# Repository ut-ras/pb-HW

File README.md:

# pb-HW
Hardware for PacBot 2018

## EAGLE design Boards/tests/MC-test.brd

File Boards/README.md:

### Boards:

PCBs used (or designed for) [PacBot](https://harvardrobotics.com/pacbots/).

Tests:

- MC-test
    + A feature filled breakout board for the DRV8871 (doesn't work).
    + 

- MC-test-simple
    + Simplified barebones breakout board for the DRV8871, does work.

Robot:

- S0: Stage 0 PCB
    + Has shiny (16 APA102s), 2 voltage regulators (TPS76801QD), 2 ADCs (ADS1000), battery leads, an enable jumper, and passthrough pins for I2C, 5V, battery power, and SPI (CLK/MOSI).

- S0R: Stage 0 PCB, reduced
    + Same as above minus one voltage regulator and the enable jumper.
    + This board was tested; it likely has some cap ESR issues.

- S1: Stage 1 PCB
    + 4 Motor Drivers (DRV8871s), IMU (MPU-6050), Pololu Encoder module passthrough, and two I2C bus passthrough.
    + Janky but functional.
    + 

- Stage2_V2
    + 4 Distance Sensors + EN pin (VL6180Xs), an RPi Zero W, and 4 Motor PWM output pairs, 4 Quadrature Encoder inputs, 2 I2C Bus inputs, 1 SPI input (CLK/MOSI), 1 MPU interrupt pin, and assorted power connectors.
    + Not finished or routed, but a valiant effort regardless.

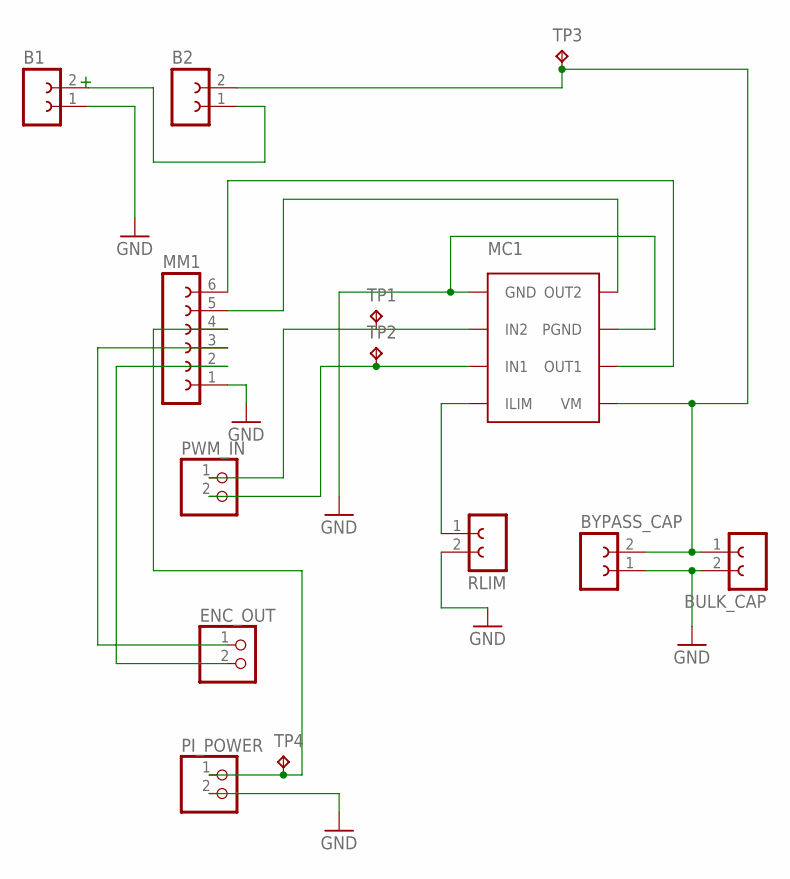
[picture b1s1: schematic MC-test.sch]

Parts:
B1, B2: FH_02X01
BULK_CAP: FH_02X01
BYPASS_CAP: FH_02X01
ENC_OUT: PINHD-1X2; 1X02
MC1: DRV8871; SO-8_POWERPAD
MM1: FE06-1; FE06
PI_POWER: PINHD-1X2; 1X02
PWM_IN: PINHD-1X2; 1X02
RLIM: FH_02X01
TP1, TP2, TP3, TP4: TPTP15SQ; TP15SQ

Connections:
3.3V: MM1.4, PI_POWER.1, TP4.TP
GND: B1.1, BULK_CAP.2, BYPASS_CAP.1, MC1.1 (GND), MC1.7 (PGND), MM1.1, PI_POWER.2, RLIM.2
M+: MC1.8 (OUT2), MM1.5
unnamed: ENC_OUT.1, MM1.3
unnamed: MC1.6 (OUT1), MM1.6
unnamed: B1.2, B2.1
unnamed: B2.2, BULK_CAP.1, BYPASS_CAP.2, MC1.5 (VM), TP3.TP
unnamed: MC1.4 (ILIM), RLIM.1
unnamed: ENC_OUT.2, MM1.2
unnamed: MC1.3 (IN1), PWM_IN.2, TP2.TP
unnamed: MC1.2 (IN2), PWM_IN.1, TP1.TP

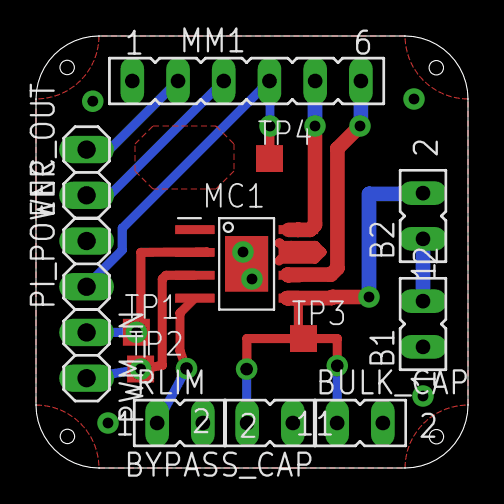
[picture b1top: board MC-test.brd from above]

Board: 2 copper layers, 24.0 x 24.0 mm, 14 parts (0 on the bottom side), 11 nets.

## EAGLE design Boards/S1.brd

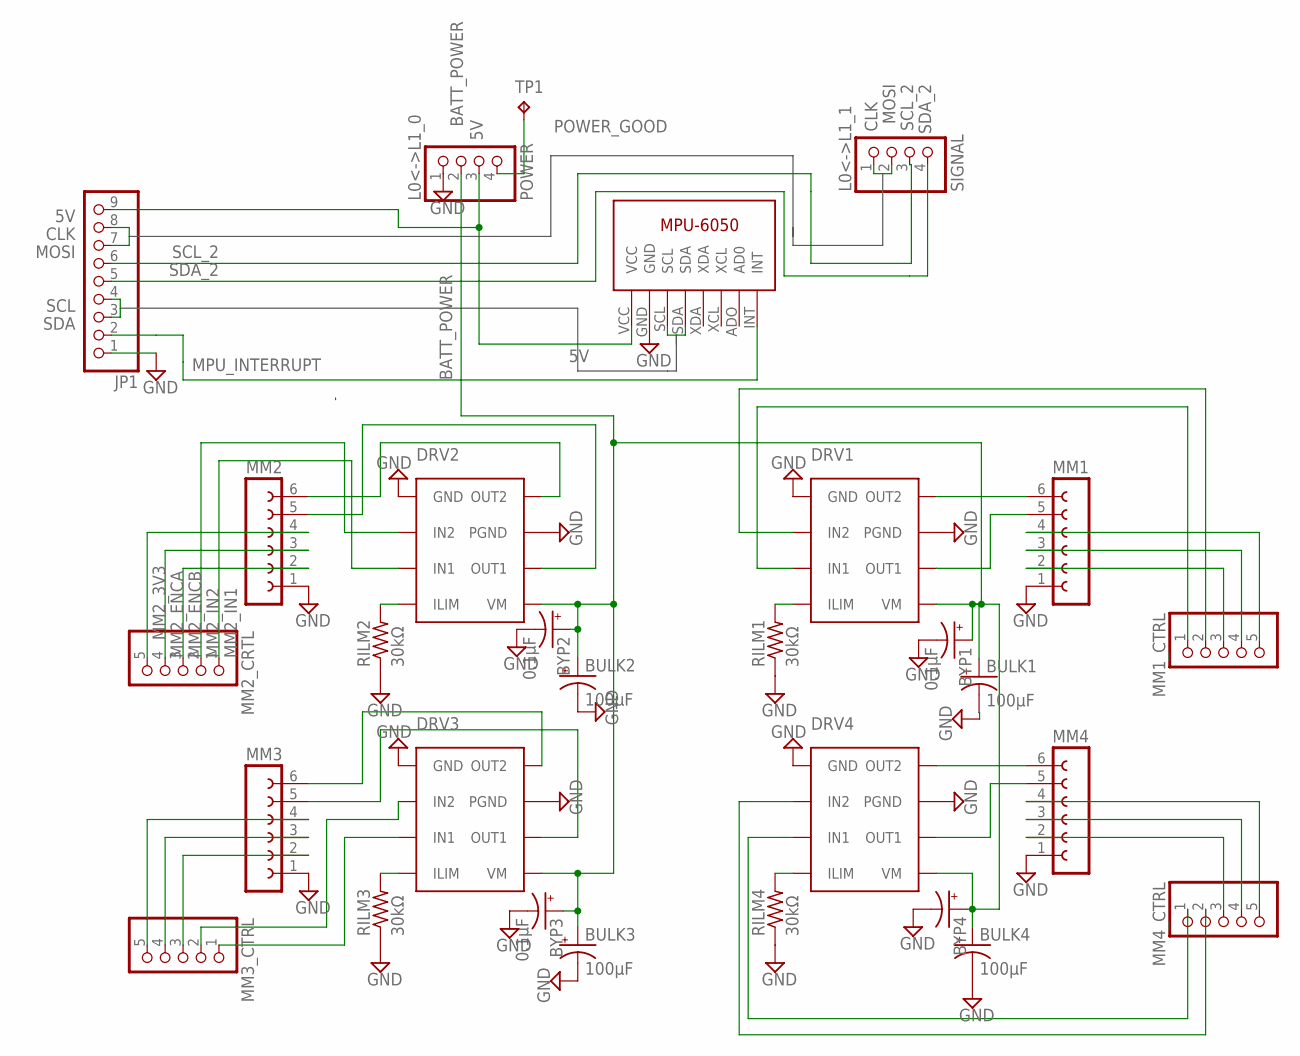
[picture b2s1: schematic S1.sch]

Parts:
BULK1, BULK2, BULK3, BULK4: 100μF; 153CLV-0605
BYP1, BYP2, BYP3: 0.1µF; A/3216-18R
BYP4: CPOL-USA/3216-18R; A/3216-18R
DRV1, DRV2, DRV3, DRV4: DRV8871; SO-8_POWERPAD
JP1: PINHD-1X9; 1X09
L0<->L1_0: POWER; 1X04/90
L0<->L1_1: SIGNAL; 1X04/90
MM1, MM2, MM3, MM4: FE06-1; FE06
MM1_CTRL, MM2_CRTL, MM3_CTRL, MM4_CTRL: PINHD-1X5; 1X05
RILM1, RILM2, RILM3, RILM4: 30kΩ; M1206
TP1: TPTP18R; TP18R
U$1: GY-521_MPUP6050; GY-521

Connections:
5V: JP1.9, L0<->L1_0.3, U$1.VCC
BATT_POWER: BULK1.+, BULK2.+, BULK3.+, BULK4.+, BYP1.+, BYP2.+, BYP3.+, BYP4.+, DRV1.5 (VM), DRV2.5 (VM), DRV3.5 (VM), DRV4.5 (VM), L0<->L1_0.2
CLK: JP1.8, L0<->L1_1.1
GND: BULK1.-, BULK2.-, BULK3.-, BULK4.-, BYP1.-, BYP2.-, BYP3.-, BYP4.-, DRV1.1 (GND), DRV1.7 (PGND), DRV2.1 (GND), DRV2.7 (PGND), DRV3.1 (GND), DRV3.7 (PGND), DRV4.1 (GND), DRV4.7 (PGND), JP1.1, L0<->L1_0.1, MM1.1, MM2.1, MM3.1, MM4.1, RILM1.1, RILM2.1, RILM3.1, RILM4.1, U$1.GND
IN1: DRV4.3 (IN1), MM4_CTRL.1
IN2: DRV4.2 (IN2), MM4_CTRL.2
MM2_3V3: MM2.4, MM2_CRTL.5
MM2_ENCA: MM2.3, MM2_CRTL.4
MM2_ENCB: MM2.2, MM2_CRTL.3
MM2_IN1: DRV2.3 (IN1), MM2_CRTL.1
MM2_IN2: DRV2.2 (IN2), MM2_CRTL.2
MOSI: JP1.7, L0<->L1_1.2
MPU_INTERRUPT: JP1.2, U$1.INT
unnamed: DRV3.4 (ILIM), RILM3.2
unnamed: DRV2.4 (ILIM), RILM2.2
unnamed: DRV1.4 (ILIM), RILM1.2
unnamed: DRV4.4 (ILIM), RILM4.2
unnamed: DRV4.8 (OUT2), MM4.6
unnamed: DRV3.6 (OUT1), MM3.5
unnamed: MM3.4, MM3_CTRL.5
unnamed: MM3.3, MM3_CTRL.4
unnamed: MM1.4, MM1_CTRL.5
unnamed: MM4.2, MM4_CTRL.3
unnamed: MM3.2, MM3_CTRL.3
unnamed: MM4.4, MM4_CTRL.5
unnamed: DRV2.8 (OUT2), MM2.6
unnamed: DRV2.6 (OUT1), MM2.5
unnamed: DRV3.8 (OUT2), MM3.6
unnamed: DRV4.6 (OUT1), MM4.5
unnamed: DRV1.6 (OUT1), MM1.5
unnamed: DRV1.8 (OUT2), MM1.6
unnamed: DRV3.2 (IN2), MM3_CTRL.2
unnamed: DRV3.3 (IN1), MM3_CTRL.1
unnamed: MM1.3, MM1_CTRL.4
unnamed: MM1.2, MM1_CTRL.3
unnamed: DRV1.2 (IN2), MM1_CTRL.2
unnamed: DRV1.3 (IN1), MM1_CTRL.1
unnamed: MM4.3, MM4_CTRL.4
POWER_GOOD: L0<->L1_0.4, TP1.TP
SCL: JP1.4, U$1.SCL
SCL_2: JP1.6, L0<->L1_1.3
SDA: JP1.3, U$1.SDA
SDA_2: JP1.5, L0<->L1_1.4

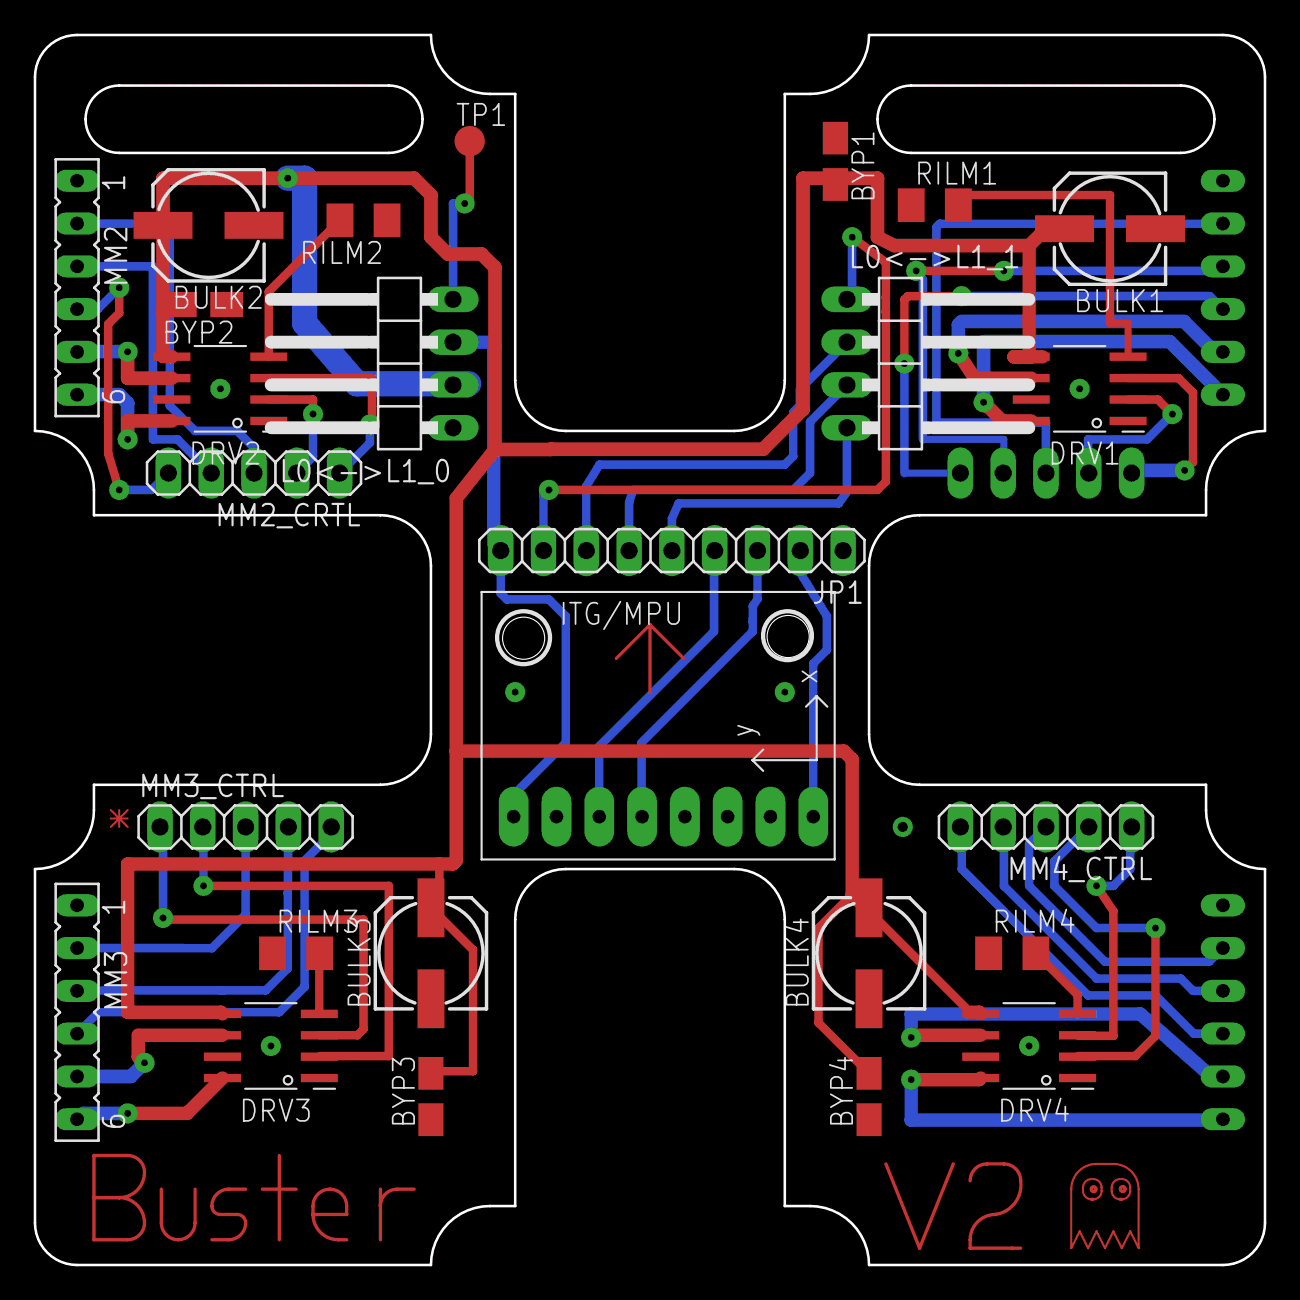
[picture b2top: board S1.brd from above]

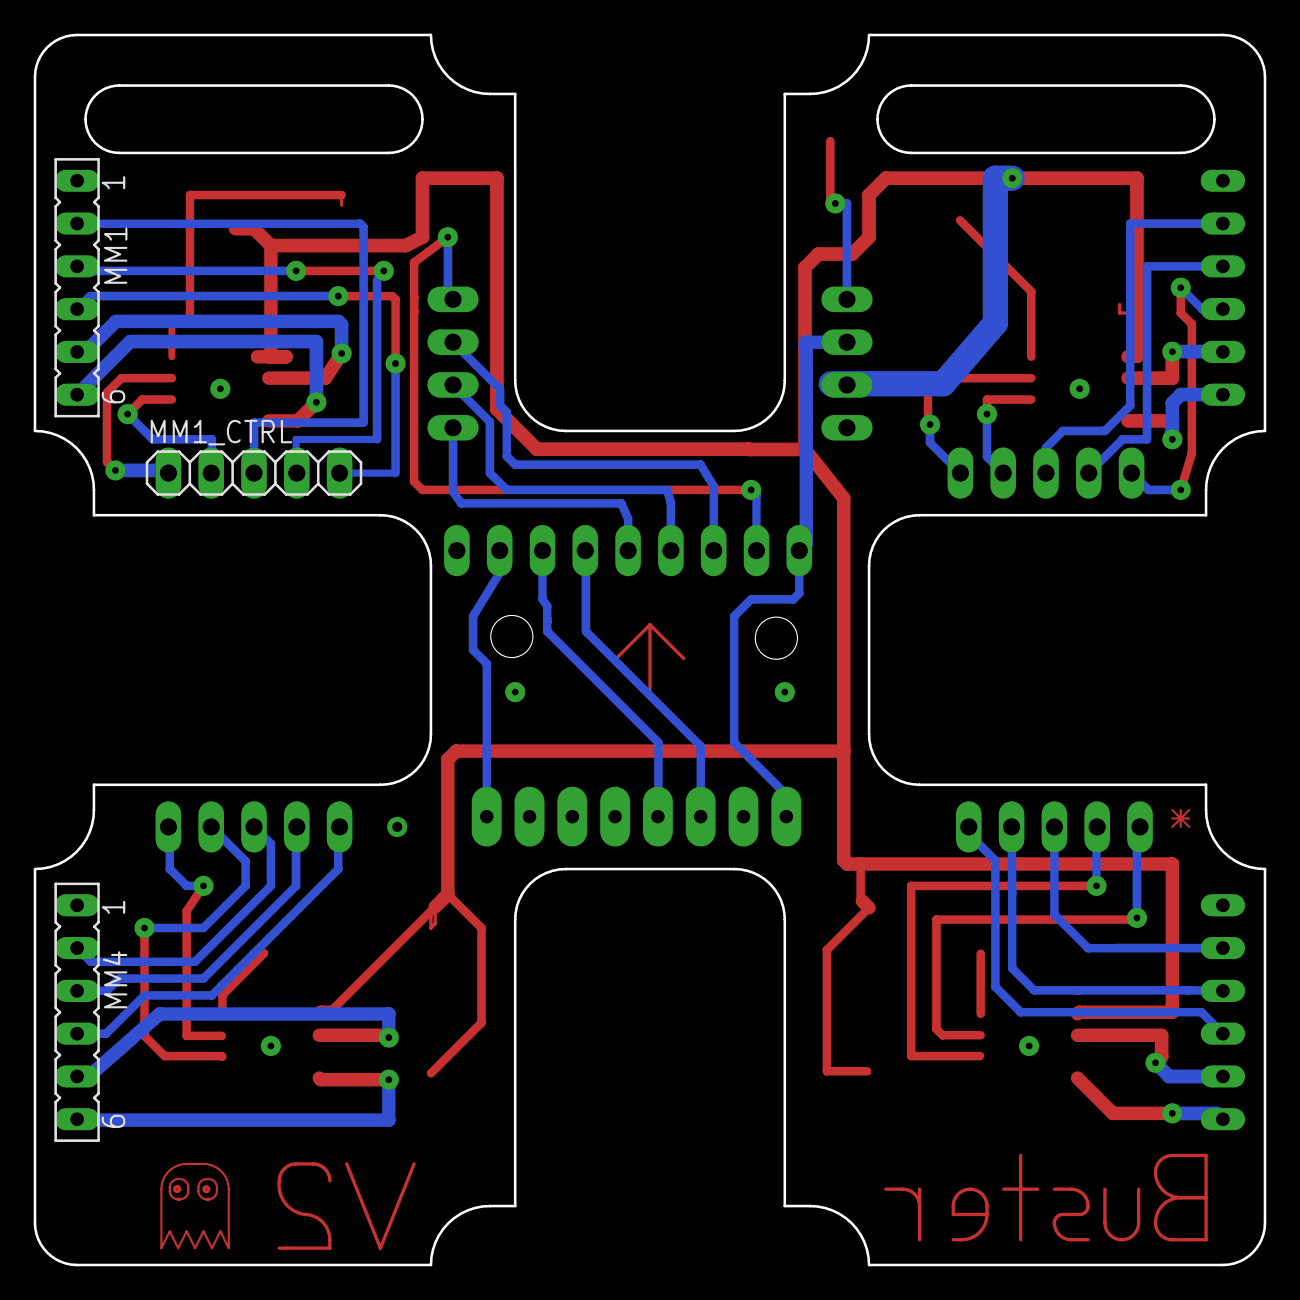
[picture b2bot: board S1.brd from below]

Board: 2 copper layers, 73.0 x 73.0 mm, 29 parts (3 on the bottom side), 43 nets.

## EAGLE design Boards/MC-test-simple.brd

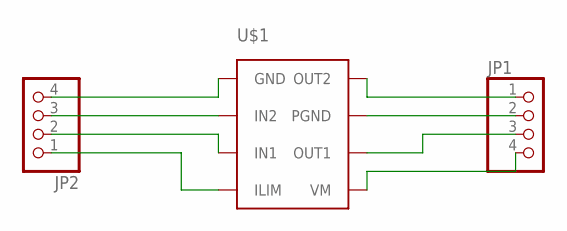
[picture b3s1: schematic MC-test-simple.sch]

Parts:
JP1, JP2: PINHD-1X4; 1X04
U$1: DRV8871; SO-8_POWERPAD

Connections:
GND: JP1.2, JP2.4, U$1.1 (GND), U$1.7 (PGND)
ILIM: JP2.1, U$1.4 (ILIM)
IN1: JP2.2, U$1.3 (IN1)
IN2: JP2.3, U$1.2 (IN2)
OUT1: JP1.3, U$1.6 (OUT1)
OUT2: JP1.1, U$1.8 (OUT2)
VM: JP1.4, U$1.5 (VM)

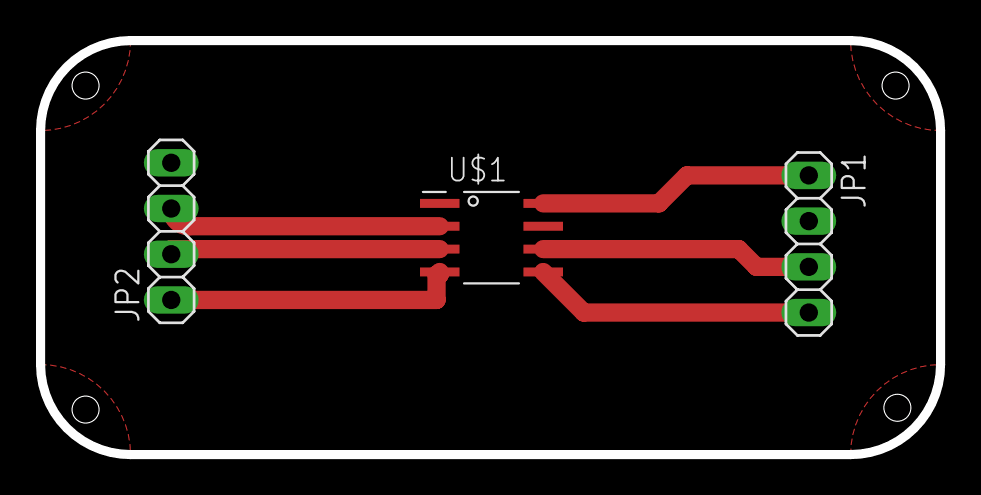
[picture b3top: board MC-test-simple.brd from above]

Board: 2 copper layers, 50.0 x 23.0 mm, 3 parts (0 on the bottom side), 7 nets.

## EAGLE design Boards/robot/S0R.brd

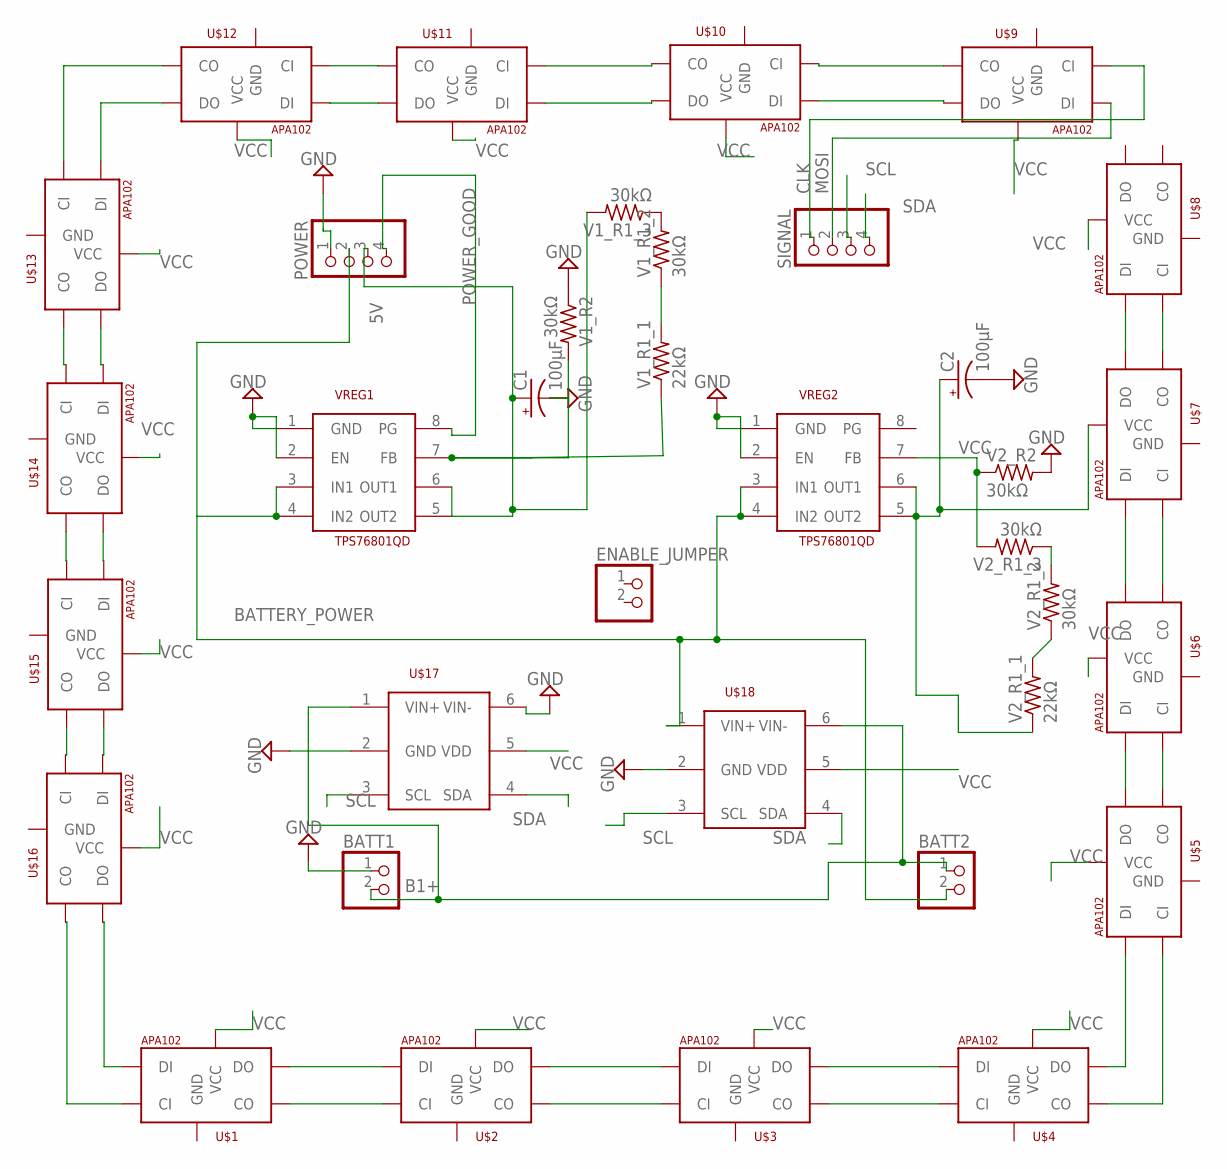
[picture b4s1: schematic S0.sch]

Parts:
BATT1, BATT2: PINHD-1X2/90; 1X02/90
C1, C2: 100µF; D/7343-31R
ENABLE_JUMPER: PINHD-1X2/90; 1X02/90
POWER: PINHD-1X4; 1X04
SIGNAL: PINHD-1X4; 1X04
U$1, U$2, U$3, U$4, U$5, U$6, U$7, U$8, U$9, U$10, U$11, U$12, U$13, U$14, U$15, U$16: APA1025050; APA102_5050
U$17: ADS1000BD0; SOT-23-6-DBV
U$18: ADS1000BD1; SOT-23-6-DBV
V1_R1_1, V2_R1_1: 22kΩ; R0402
V1_R1_2, V1_R1_3, V1_R2, V2_R1_2, V2_R1_3, V2_R2: 30kΩ; M1206
VREG1, VREG2: TPS76801QD; SO-8_POWERPAD

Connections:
5V: C1.+, POWER.3, V1_R1_3.2, VREG1.5 (OUT2), VREG1.6 (OUT1)
B1+: BATT1.2, BATT2.1, U$17.1 (VIN+), U$18.6 (VIN-)
BATTERY_POWER: BATT2.2, POWER.2, U$18.1 (VIN+), VREG1.3 (IN1), VREG1.4 (IN2), VREG2.3 (IN1), VREG2.4 (IN2)
CLK: SIGNAL.1, U$9.5 (CI)
GND: BATT1.1, C1.-, C2.-, POWER.1, U$1.6 (GND), U$2.6 (GND), U$3.6 (GND), U$4.6 (GND), U$5.6 (GND), U$6.6 (GND), U$7.6 (GND), U$8.6 (GND), U$9.6 (GND), U$10.6 (GND), U$11.6 (GND), U$12.6 (GND), U$13.6 (GND), U$14.6 (GND), U$15.6 (GND), U$16.6 (GND), U$17.2 (GND), U$17.6 (VIN-), U$18.2 (GND), V1_R2.1, V2_R2.2, VREG1.1 (GND), VREG1.2 (EN), VREG2.1 (GND), VREG2.2 (EN)
MOSI: SIGNAL.2, U$9.4 (DI)
unnamed: U$1.3 (DO), U$2.4 (DI)
unnamed: U$1.2 (CO), U$2.5 (CI)
unnamed: U$2.3 (DO), U$3.4 (DI)
unnamed: U$2.2 (CO), U$3.5 (CI)
unnamed: U$3.3 (DO), U$4.4 (DI)
unnamed: U$3.2 (CO), U$4.5 (CI)
unnamed: U$4.3 (DO), U$5.4 (DI)
unnamed: U$4.2 (CO), U$5.5 (CI)
unnamed: U$5.2 (CO), U$6.5 (CI)
unnamed: U$5.3 (DO), U$6.4 (DI)
unnamed: U$6.3 (DO), U$7.4 (DI)
unnamed: U$6.2 (CO), U$7.5 (CI)
unnamed: U$7.2 (CO), U$8.5 (CI)
unnamed: U$7.3 (DO), U$8.4 (DI)
unnamed: U$1.5 (CI), U$16.2 (CO)
unnamed: U$1.4 (DI), U$16.3 (DO)
unnamed: U$9.3 (DO), U$10.4 (DI)
unnamed: U$9.2 (CO), U$10.5 (CI)
unnamed: U$10.2 (CO), U$11.5 (CI)
unnamed: U$10.3 (DO), U$11.4 (DI)
unnamed: U$11.2 (CO), U$12.5 (CI)
unnamed: U$11.3 (DO), U$12.4 (DI)
unnamed: U$12.2 (CO), U$13.5 (CI)
unnamed: U$12.3 (DO), U$13.4 (DI)
unnamed: U$13.3 (DO), U$14.4 (DI)
unnamed: U$13.2 (CO), U$14.5 (CI)
unnamed: U$14.3 (DO), U$15.4 (DI)
unnamed: U$14.2 (CO), U$15.5 (CI)
unnamed: U$15.2 (CO), U$16.5 (CI)
unnamed: U$15.3 (DO), U$16.4 (DI)
unnamed: V2_R1_2.2, V2_R1_3.1
unnamed: V1_R1_1.2, V1_R1_2.1
unnamed: V1_R1_1.1, V1_R2.2, VREG1.7 (FB)
unnamed: V1_R1_2.2, V1_R1_3.1
unnamed: V2_R1_1.2, V2_R1_2.1
unnamed: V2_R1_3.2, V2_R2.1, VREG2.7 (FB)
POWER_GOOD: POWER.4, VREG1.8 (PG)
SCL: SIGNAL.3, U$17.3 (SCL), U$18.3 (SCL)
SDA: SIGNAL.4, U$17.4 (SDA), U$18.4 (SDA)
VCC: C2.+, U$1.1 (VCC), U$2.1 (VCC), U$3.1 (VCC), U$4.1 (VCC), U$5.1 (VCC), U$6.1 (VCC), U$7.1 (VCC), U$8.1 (VCC), U$9.1 (VCC), U$10.1 (VCC), U$11.1 (VCC), U$12.1 (VCC), U$13.1 (VCC), U$14.1 (VCC), U$15.1 (VCC), U$16.1 (VCC), U$17.5 (VDD), U$18.5 (VDD), V2_R1_1.1, VREG2.5 (OUT2), VREG2.6 (OUT1)

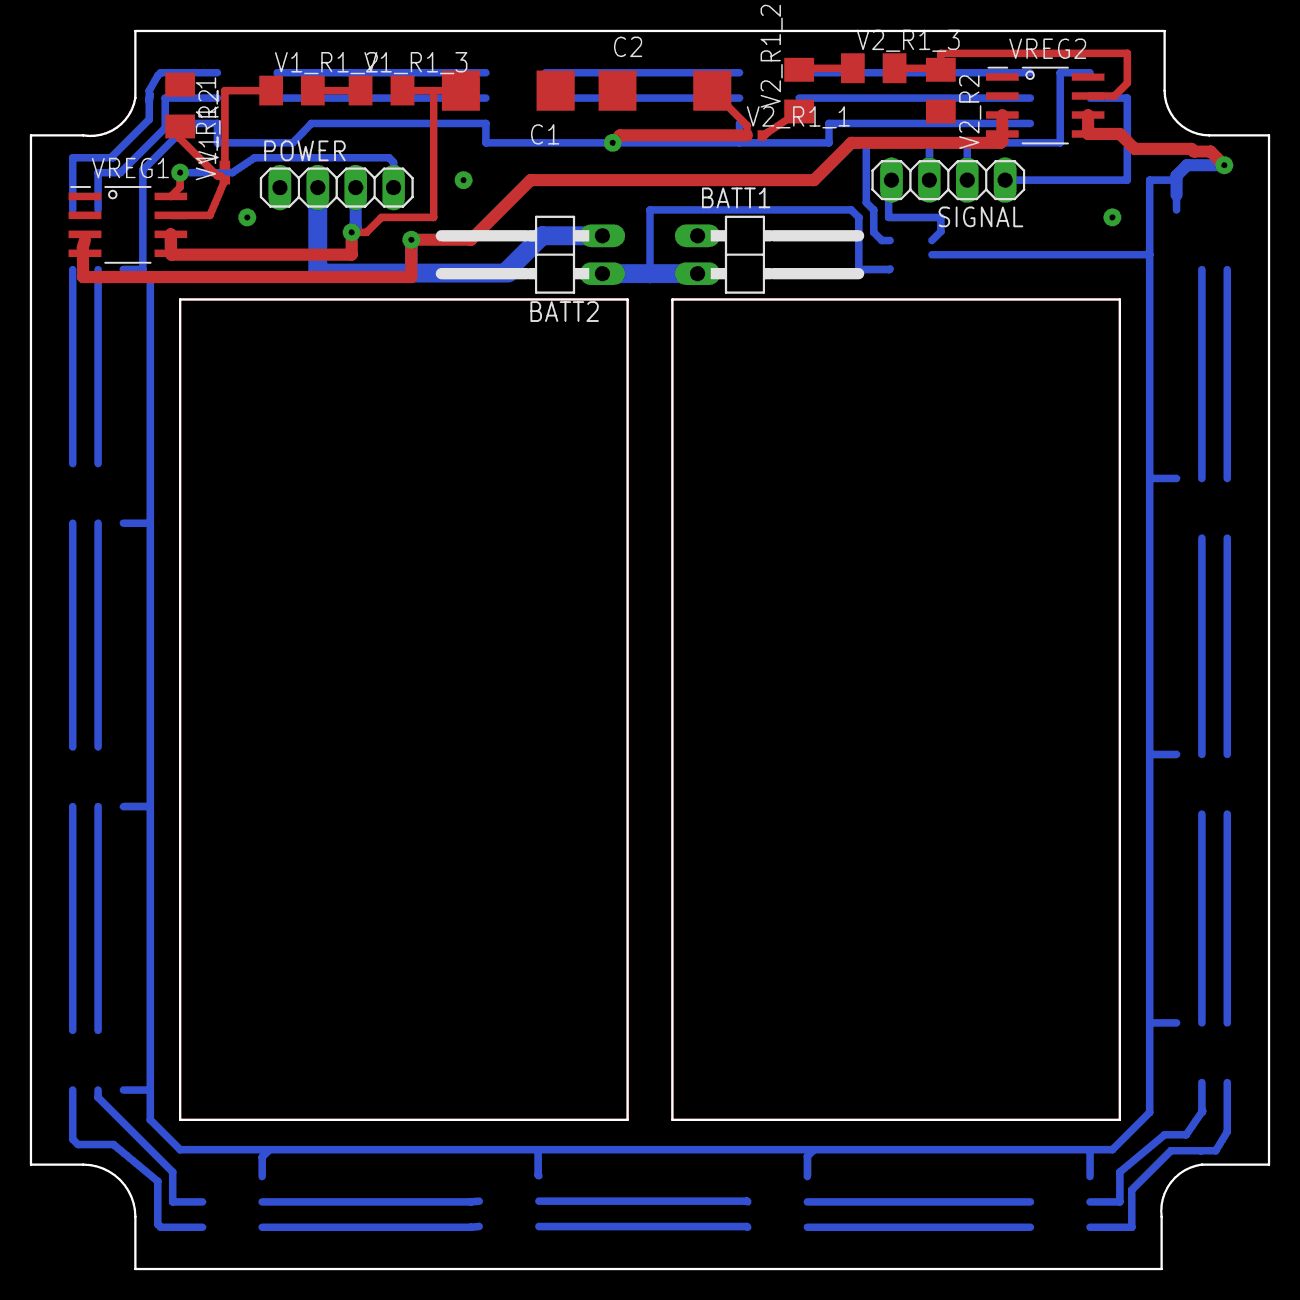
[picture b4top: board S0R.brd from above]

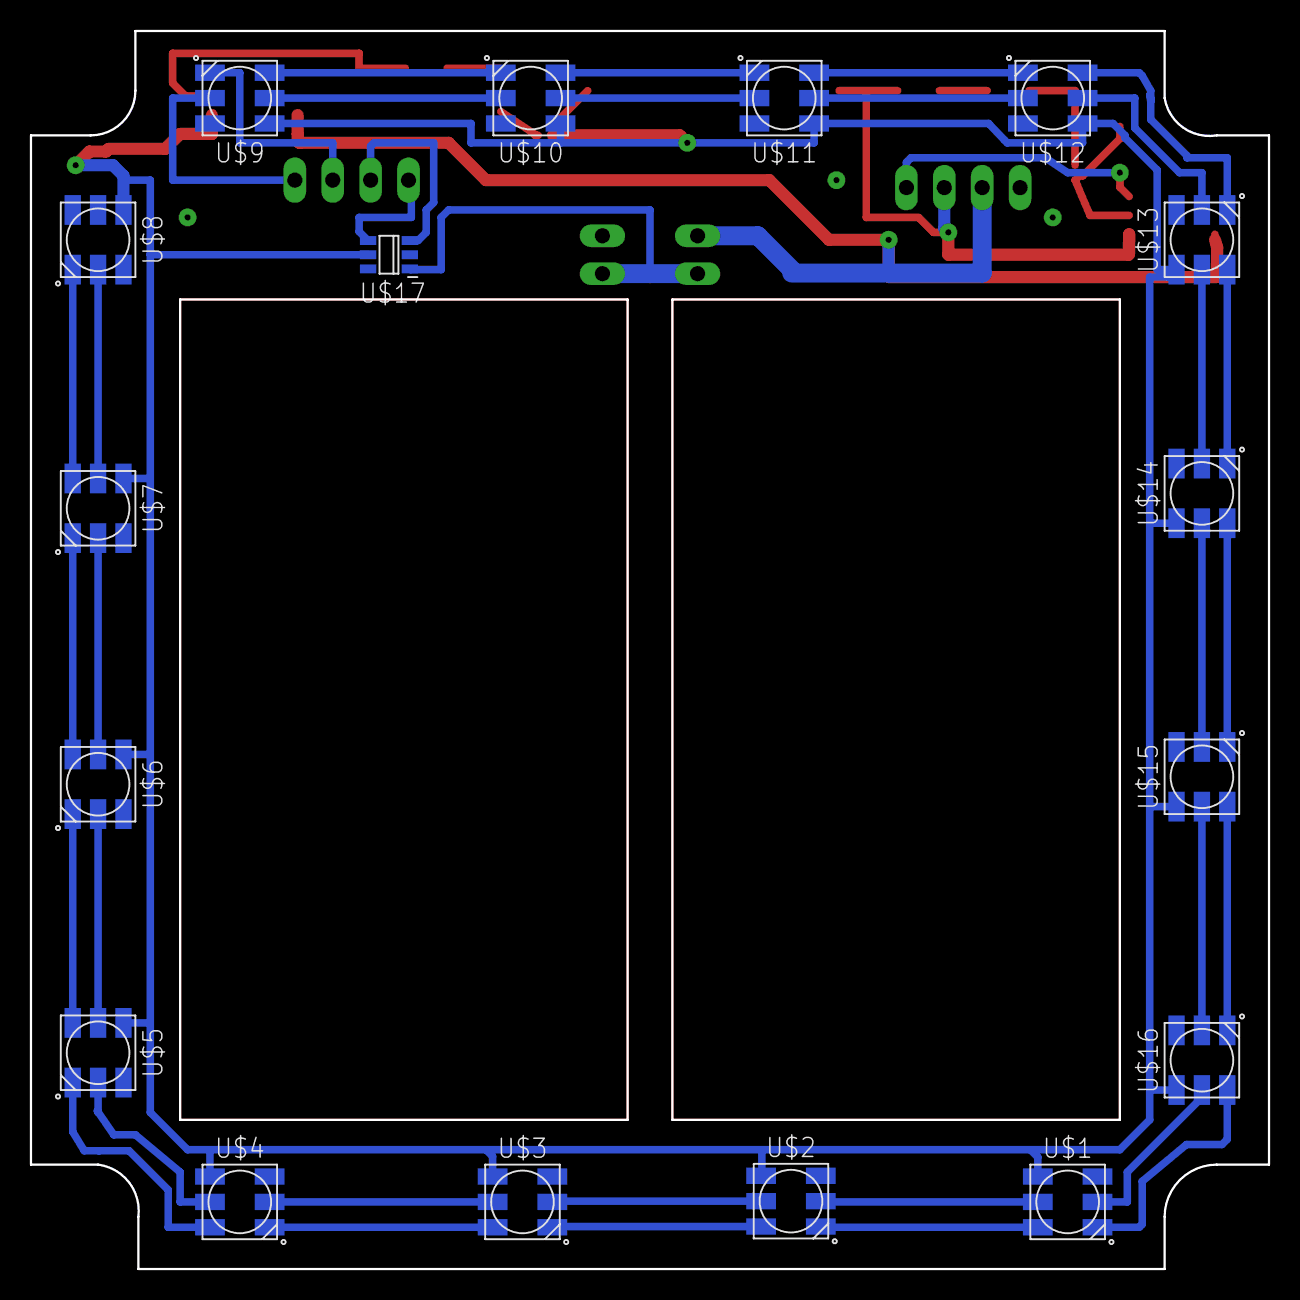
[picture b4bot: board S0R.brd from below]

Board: 2 copper layers, 83.0 x 83.0 mm, 33 parts (17 on the bottom side), 46 nets.

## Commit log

2018-04-29 Old version of the Parts library (pre-management)
2018-04-29 Overengineered DRV8871 Test Board
    It didn't literally go up in flames but we got pretty close
2018-04-29 A glorified DRV8871 breakout
    (it works!)
2018-04-29 Stage 1 of Buster
    Hacky and a manufacturing nightmare but undeniably functional
2018-04-29 The mostly complete vision for Buster V2's Stage 0
    (has the enable jumper + the 2nd ADC)
2018-04-29 The reduced version of the Stage 0 PCB
    Functional-ish? ADC was never tested, lights were scorchy (probably because of the TPS) and caps are probably wrong (ESR too high).
    Makes a very spiffy battery carriage however.
2018-04-29 The (incomplete) Stage 2 PCB from Miguel
    Never finished, but a valiant effort nonetheless
2018-04-29 Restructuring
2018-04-29 Add images
2018-04-29 Add updated version of the Parts library
    Contains:
    - ADS1000
    - APA102
    - BQ28Z610
    - MPU6050 (GY-521 breakout)
    - RPi Zero
2018-04-29 Add some info
2018-04-29 Kanishka's Fusion 360 files from GDrive
    Eventually these should be .stls
